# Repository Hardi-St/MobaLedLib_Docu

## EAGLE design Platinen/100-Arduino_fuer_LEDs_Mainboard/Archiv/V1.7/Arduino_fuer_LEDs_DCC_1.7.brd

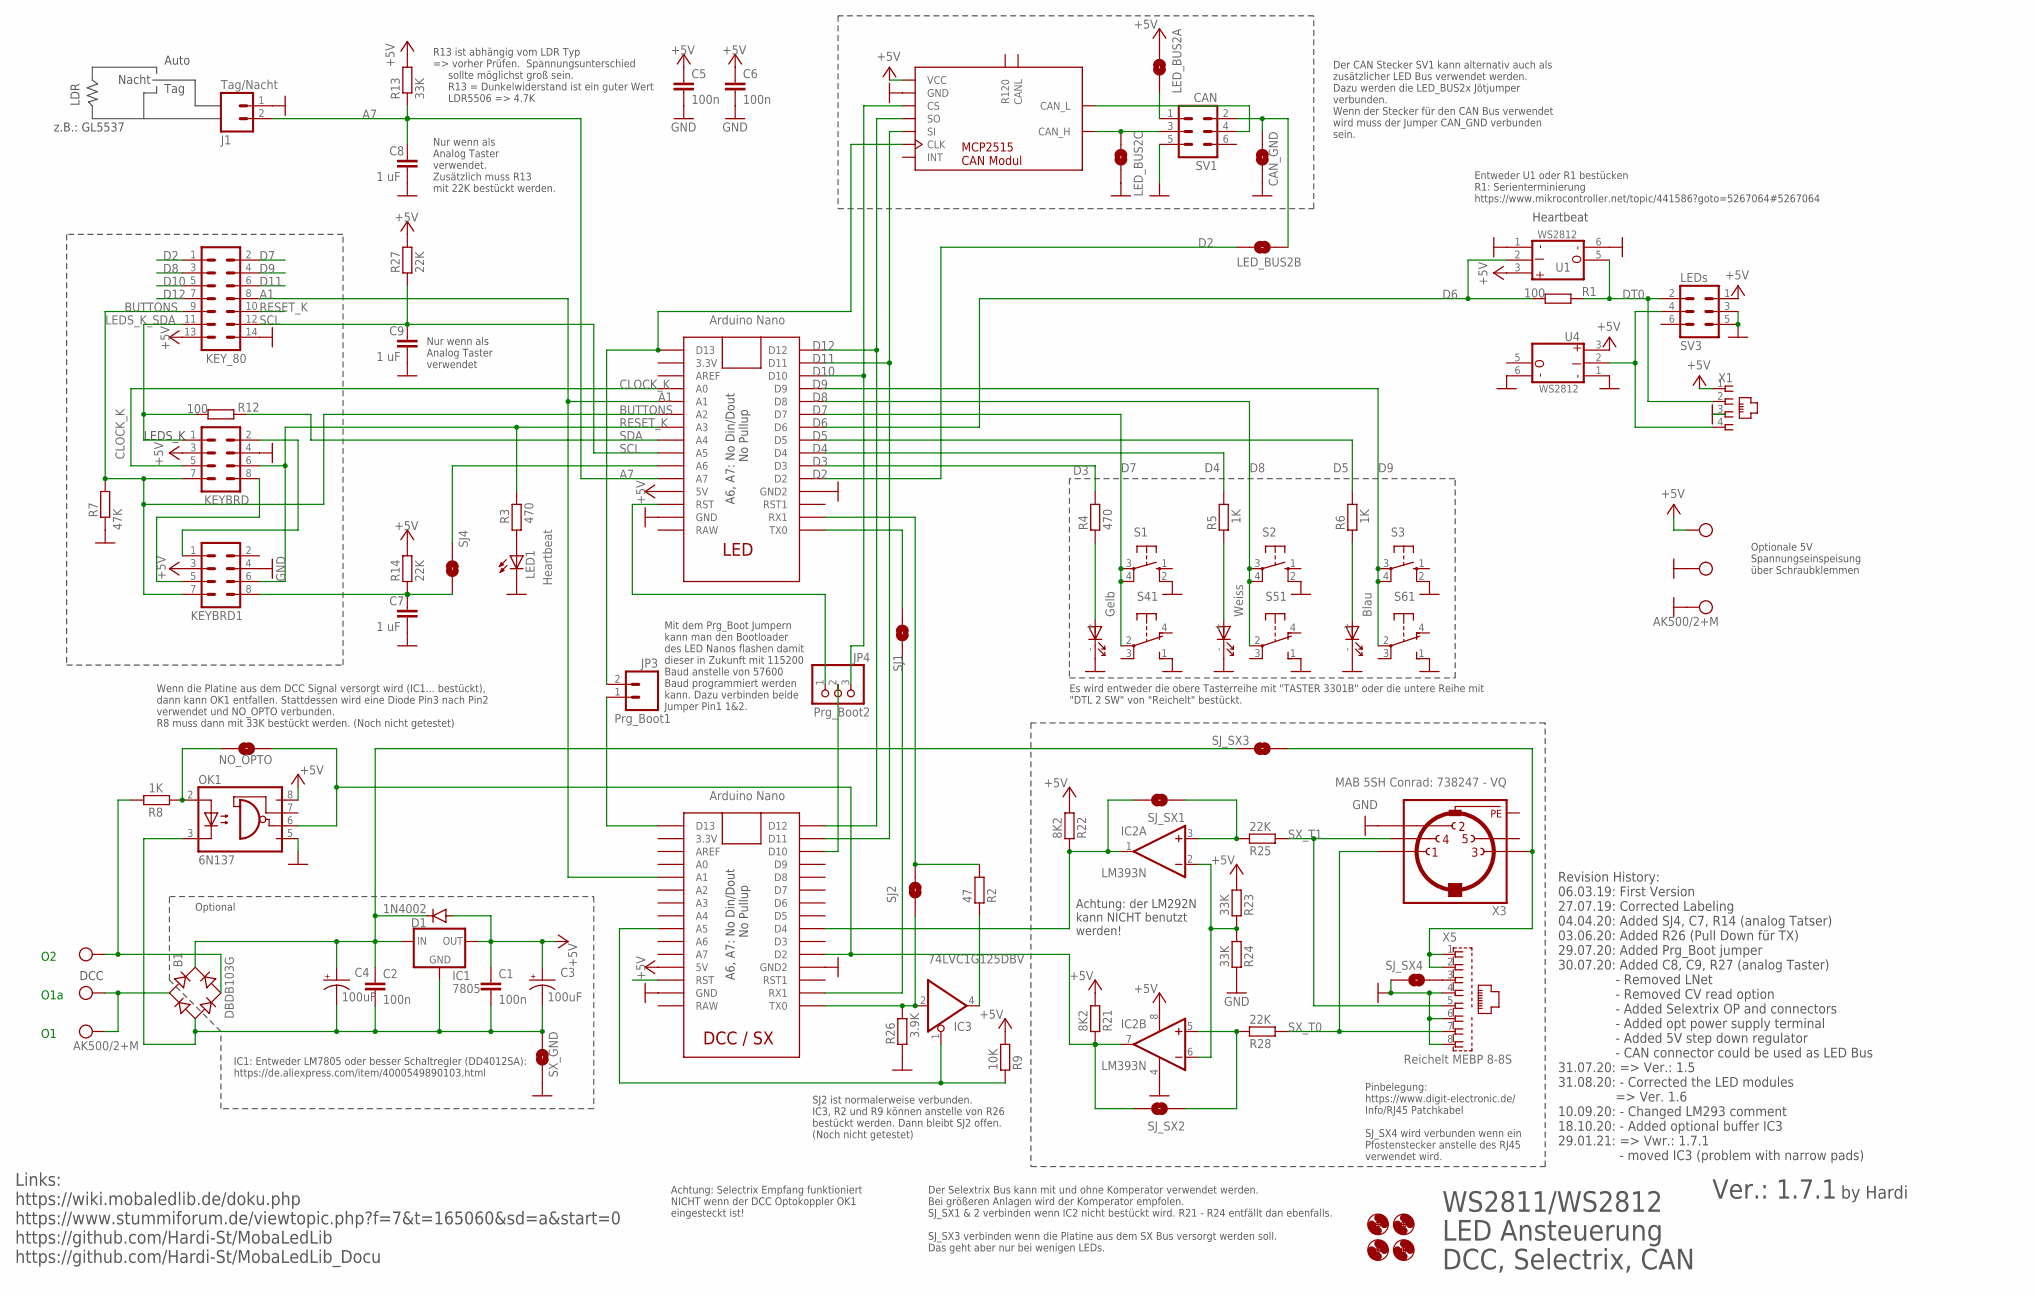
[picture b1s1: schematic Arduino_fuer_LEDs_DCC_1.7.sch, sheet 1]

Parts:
B1: DBDB103G; DB
C1, C2, C5, C6: 100n; C025-025X050
C3, C4: 100uF; SPARKFUN-CAPACITORS_CPOL-RADIAL-100UF-25V
C7, C8, C9: 1 uF; C025-025X050
CAN2: MCP2515_CAN_MODUL
CAN_GND: SOLDERJUMPERNO; SJ_2S-NO
D1: 1N4002; DO41-10
H1, H2, H3, H4: MOUNT-HOLE3.0; 3,0
IC1: 7805; 78XXS
IC2: LM393N; DIL08
IC3: 74LVC1G125DBV; SOT23-5
J1: Tag/Nacht; 1X02
JP3: Prg_Boot1; 1X02
JP4: Prg_Boot2; 1X03-CLEANBIG
KEYBRD, KEYBRD1: CON-HARTING-ML_ML08
KEY_80: ML14
LED1: Heartbeat; LED3MM
LED_BUS2A, LED_BUS2B, LED_BUS2C: SOLDERJUMPERNO; SJ_2S-NO
NO_OPTO: SOLDERJUMPERNO; SJ_2S-NO
OK1: 6N137; DIL08
R1, R12: 100; 0204/7
R2: 47; 0204/7
R3, R4: 470; 0204/7
R5, R6, R8: 1K; 0204/7
R7: 47K; 0204/7
R9: 10K; 0204/5
R13: 33K; 0204/7
R14, R27: 22K; 0204/7
R21, R22: 8K2; 0207/2V
R23, R24: 33K; 0207/2V
R25, R28: 22K; 0207/2V
R26: 3.9K; 0204/7
S1, S2, S3: 10-XX; B3F-10XX
S4: Gelb; SRKL
S5: Weiss; SRKL
S6: Blau; SRKL
SJ1, SJ2, SJ4: SOLDERJUMPERNO; SJ_2S-NO
SJ_SX1, SJ_SX2, SJ_SX3, SJ_SX4: SOLDERJUMPERNO; SJ_2S-NO
SV1: CAN; ML6
SV3: LEDs; ML6
SX_GND: SOLDERJUMPERNO; SJ_2S-NO
U1, U4: WS2812_MODUL; WS2812_LED_MODUL
U2: LED NANO; NANO
U3: DCC NANO; NANO
X1: RJ10
X2, X4: AK500/2+M
X3: MAB 5SH Conrad: 738247 - VQ; MAB5SH
X5: Reichelt MEBP 8-8S; RJ45_MEBP8-8S

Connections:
+5V: C1.1, C3.1 (+), C5.1, C6.1, CAN2.1 (VCC), D1.A, IC1.OUT, IC2.8 (V+), IC3.5 (VCC), KEYBRD.3, KEYBRD1.3, KEY_80.13, LED_BUS2A.1, OK1.8 (VCC), R9.2, R13.2, R14.2, R21.2, R22.2, R23.2, R27.2, SV3.1, U1.3 (VDD), U2.5V, U3.5V, U4.3 (VDD), X1.1, X4.2; also elsewhere on the board
A1: KEY_80.8, U2.A1, U3.A1
A7: C8.1, J1.2, R13.1, U2.A7
BUTTONS: KEYBRD.7, KEYBRD1.7, KEY_80.9, R7.2, U2.A2
CAN_H: CAN2.9 (CAN_H), LED_BUS2C.1, SV1.3
CAN_L: CAN2.8 (CAN_L), SV1.4
CLOCK_K: KEYBRD.5, U2.A0
D2: KEY_80.1, LED_BUS2B.1, U2.D2
D3: R4.2, U2.D3
D4: R5.2, U2.D4
D5: R6.2, U2.D5
D6: R1.2, U1.2 (DIN), U2.D6
D7: KEY_80.2, S1.3, S1.4 (P1), S4.2, U2.D7
D8: KEY_80.3, S2.3, S2.4 (P1), S5.2, U2.D8
D9: KEY_80.4, S3.3, S3.4 (P1), S6.2, U2.D9
D10: CAN2.3 (CS), JP4.3, KEY_80.5, U2.D10
D11: CAN2.5 (SI), KEY_80.6, U2.D11, U3.D11
D12: CAN2.4 (SO), KEY_80.7, U2.D12, U3.D12
DT0: R1.1, SV3.2, U1.5 (DO), X1.2; also elsewhere on the board
GND: C5.2, C6.2, C7.2, C8.2, C9.2, CAN2.2 (GND), CAN_GND.2, IC2.4 (V-), IC3.3 (GND), J1.1, KEYBRD.4, KEYBRD1.4, KEY_80.14, LED1.K (C), LED_BUS2C.2, OK1.5 (GND), R7.1, R24.1, R26.1, S1.2 (S1), S2.2 (S1), S3.2 (S1), S4.1 (S), S4.- (C), S5.1 (S), S5.- (C), S6.1 (S), S6.- (C), SJ_SX4.2, SV1.5, SV3.3, SV3.5, SX_GND.2, U1.1 (GND), U1.6 (GND1), U2.GND, U2.GND1 (GND2), U3.GND, U3.GND1 (GND2), U4.1 (GND), U4.6 (GND1), X1.3, X3.2, X4.1, X4.M, X5.4, X5.6, X5.8; also elsewhere on the board
LEDS_K_SDA: KEYBRD.1, KEY_80.11, R12.2
unnamed: SJ1.2, U2.TX0
unnamed: SJ_SX4.1, X5.3
unnamed: IC3.1 (OE), R9.1, U3.A5
unnamed: R4.1, S4.+ (A)
unnamed: CAN2.6 (CLK), JP3.2, U2.D13
unnamed: R5.1, S5.+ (A)
unnamed: R6.1, S6.+ (A)
unnamed: IC2.7 (OUT), NO_OPTO.1, OK1.6 (VO), R21.1, SJ_SX2.2, U3.D2
unnamed: LED_BUS2A.2, SV1.1
unnamed: SV3.4, U4.2 (DIN), X1.4
unnamed: B1.AC2, R8.2, X2.2
unnamed: B1.AC1, X2.1, X2.M
unnamed: B1.+, C2.1, C4.1 (+), D1.C, IC1.IN, SJ_SX3.2
unnamed: JP4.1, U2.RST
unnamed: IC2.1 (OUT), R22.1, SJ_SX1.2, U3.D4
unnamed: B1.-, C1.2, C2.2, C3.2 (-), C4.2 (-), IC1.GND, OK1.3 (C), SX_GND.1
unnamed: SJ1.1, U3.RX1
unnamed: LED1.A, R3.1
unnamed: JP3.1, U3.D13
unnamed: NO_OPTO.2, OK1.2 (A), R8.1
unnamed: C7.1, KEYBRD1.8, R14.1, SJ4.2
unnamed: KEYBRD.2, KEYBRD1.1
unnamed: KEYBRD.8, KEYBRD1.5
unnamed: SJ_SX3.1, X3.3, X5.1, X5.2
unnamed: SJ4.1, U2.A6
unnamed: JP4.2, U3.D10
unnamed: CAN_GND.1, LED_BUS2B.2, SV1.2
unnamed: IC3.2 (I), R26.2, SJ2.1, U3.TX0
unnamed: IC3.4 (O), R2.1
unnamed: R2.2, SJ2.2, U2.RX1
unnamed: IC2.2 (-IN), IC2.6 (-IN), R23.1, R24.2
unnamed: IC2.3 (+IN), R25.1, SJ_SX1.1
unnamed: IC2.5 (+IN), R28.1, SJ_SX2.1
PE: X3.PE, X3.PE@ (PE)
RESET_K: KEYBRD.6, KEYBRD1.6, KEY_80.10, R3.2, U2.A3
SCL: C9.1, KEY_80.12, R27.1, U2.A5
SDA: R12.1, U2.A4
SX_T0: R28.2, X3.1, X5.7
SX_T1: R25.2, X3.4, X5.5

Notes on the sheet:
WS2811/WS2812 LED Ansteuerung DCC, Selectrix, CAN
Es wird entweder die obere Tasterreihe mit "TASTER 3301B" oder die untere Reihe mit "DTL 2 SW" von "Reichelt" bestückt.
A6, A7: No Din/Dout No Pullup
Ver.: 1.7.1
LDR
Auto
Nacht
Tag
Entweder U1 oder R1 bestücken R1: Serienterminierung https://www.mikrocontroller.net/topic/441586?goto=5267064#5267064
Heartbeat
DCC
LEDS_K
Revision History: 06.03.19: First Version 27.07.19: Corrected Labeling 04.04.20: Added SJ4, C7, R14 (analog Tatser) 03.06.20: Added R26 (Pull Down für TX) 29.07.20: Added Prg_Boot jumper 30.07.20: Added C8, C9, R27 (analog Taster) - Removed LNet - Removed CV read option - Added Selextrix OP and con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
O1a
z.B.: GL5537
R13 ist abhängig vom LDR Typ => vorher Prüfen. Spannungsunterschied sollte möglichst groß sein. R13 = Dunkelwiderstand ist ein guter Wert LDR5506 => 4.7K
Nur wenn als Analog Taster verwendet. Zusätzlich muss R13 mit 22K bestückt werden.
Optional
Nur wenn als Analog Taster verwendet
Der CAN Stecker SV1 kann alternativ auch als zusätzlicher LED Bus verwendet werden. Dazu werden die LED_BUS2x Jötjumper verbunden. Wenn der Stecker für den CAN Bus verwendet wird muss der Jumper CAN_GND verbunden sein.
Pinbelegung: https://www.digit-electronic.de/ Info/RJ45 Patchkabel SJ_SX4 wird verbunden wenn ein Pfostenstecker anstelle des RJ45 verwendet wird.
IC1: Entweder LM7805 oder besser Schaltregler (DD4012SA): https://de.aliexpress.com/item/4000549890103.html
Optionale 5V Spannungseinspeisung über Schraubklemmen
by Hardi
Links: https://wiki.mobaledlib.de/doku.php https://www.stummiforum.de/viewtopic.php?f=7&t=165060&sd=a&start=0 https://github.com/Hardi-St/MobaLedLib https://github.com/Hardi-St/MobaLedLib_Docu
Mit dem Prg_Boot Jumpern kann man den Bootloader des LED Nanos flashen damit dieser in Zukunft mit 115200 Baud anstelle von 57600 Baud programmiert werden kann. Dazu verbinden beide Jumper Pin1 1&2.
LED
DCC / SX
Der Selextrix Bus kann mit und ohne Komperator verwendet werden. Bei größeren Anlagen wird der Komperator empfolen. SJ_SX1 & 2 verbinden wenn IC2 nicht bestückt wird. R21 - R24 entfällt dan ebenfalls. SJ_SX3 verbinden wenn die Platine aus dem SX Bus versorgt werden soll. Das geht aber nur bei wenig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
Wenn die Platine aus dem DCC Signal versorgt wird (IC1... bestückt), dann kann OK1 entfallen. Stattdessen wird eine Diode Pin3 nach Pin2 verwendet und NO_OPTO verbunden. R8 muss dann mit 33K bestückt werden. (Noch nicht getestet)
Achtung: der LM292N kann NICHT benutzt werden!
SJ2 ist normalerweise verbunden. IC3, R2 und R9 können anstelle von R26 bestückt werden. Dann bleibt SJ2 offen. (Noch nicht getestet)
Achtung: Selectrix Empfang funktioniert NICHT wenn der DCC Optokoppler OK1 eingesteckt ist!

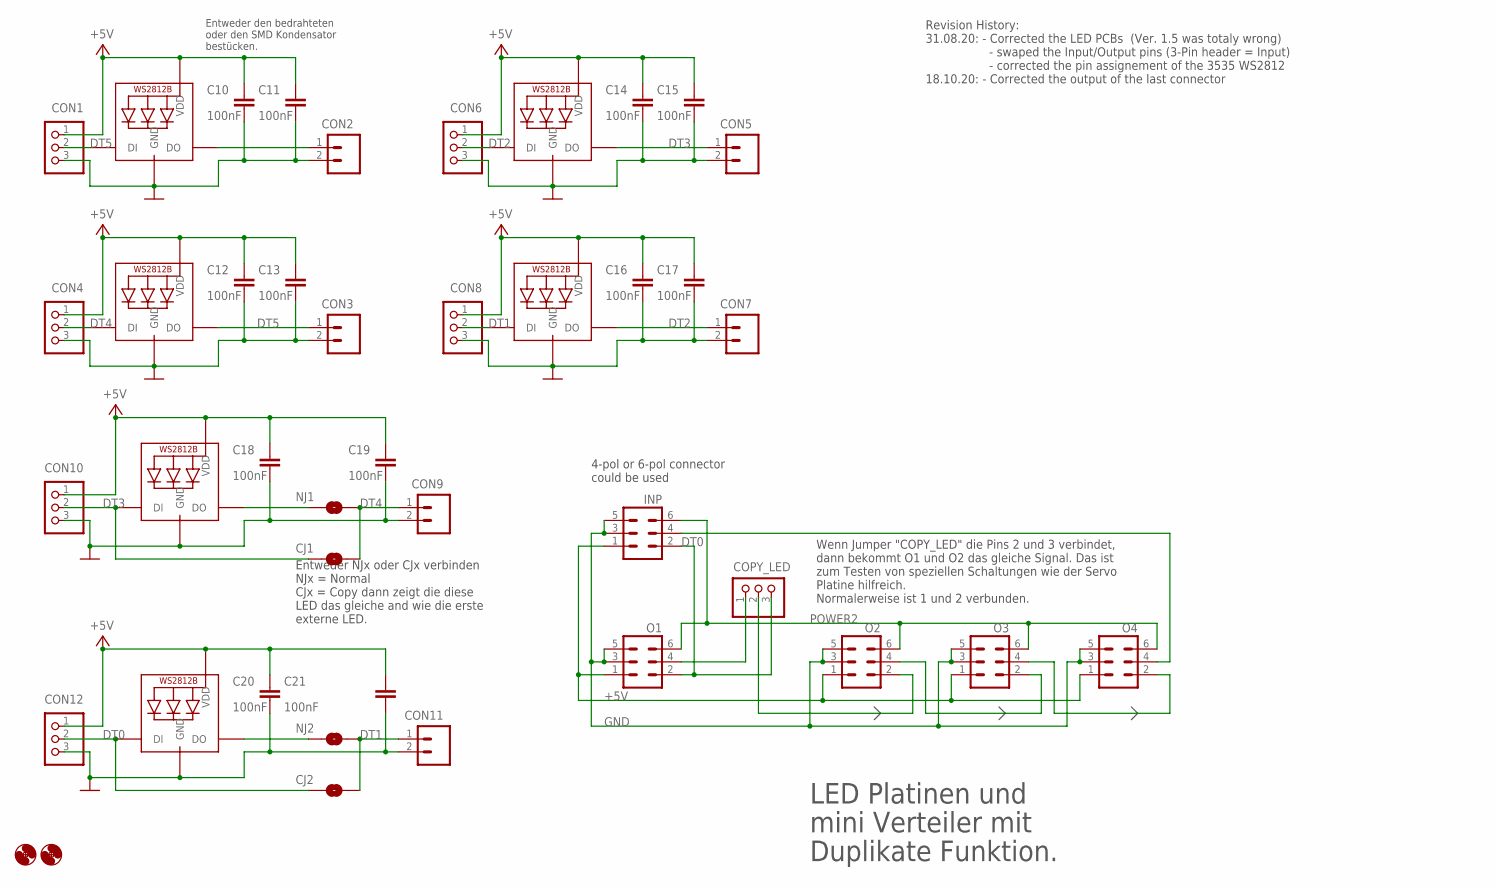
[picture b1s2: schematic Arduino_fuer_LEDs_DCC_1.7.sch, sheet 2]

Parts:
C10, C12, C14, C16, C18, C20: 100nF; C025-025X050
C11, C13, C15, C17, C19, C21: 100nF; C1206
CJ1, CJ2: SOLDERJUMPERNO; SJ_2S-NO
CON1, CON4, CON6, CON8, CON10, CON12: PINHD-1X3CB; 1X03-CLEANBIG
CON2, CON3, CON5, CON7, CON9, CON11: M02PTH; 1X02
COPY_LED: PINHD-1X3CB; 1X03-CLEANBIG
H5, H6: MOUNT-HOLE3.0; 3,0
INP: ML6
LED2, LED3, LED6: WS2812B5050; WS2812B
LED4, LED5, LED7: WS2812B3535; LED3535
NJ1, NJ2: SOLDERJUMPERNO; SJ_2S-NO
O1, O2, O3, O4: ML6

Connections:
+5V: C10.1, C11.1, C12.1, C13.1, C14.1, C15.1, C16.1, C17.1, C18.1, C19.1, C20.1, C21.1, CON1.1, CON4.1, CON6.1, CON8.1, CON10.1, CON12.1, INP.1, LED2.1-5V (VDD), LED3.1-5V (VDD), LED4.1_5V (VDD), LED5.1_5V (VDD), LED6.1-5V (VDD), LED7.1_5V (VDD), O1.1, O2.1, O3.1, O4.1; also elsewhere on the board
DT0: CJ2.1, CON12.2, COPY_LED.3, INP.2, LED7.4_DIN (DI), O1.2; also elsewhere on the board
DT1: CJ2.2, CON8.2, CON11.1, LED5.4_DIN (DI), NJ2.2
DT2: CON6.2, CON7.1, LED4.4_DIN (DI), LED5.2_DOUT (DO)
DT3: CJ1.1, CON5.1, CON10.2, LED4.2_DOUT (DO), LED6.4-DIN (DI)
DT4: CJ1.2, CON4.2, CON9.1, LED3.4-DIN (DI), NJ1.2
DT5: CON1.2, CON3.1, LED2.4-DIN (DI), LED3.2-DOUT (DO)
GND: C10.2, C11.2, C12.2, C13.2, C14.2, C15.2, C16.2, C17.2, C18.2, C19.2, C20.2, C21.2, CON1.3, CON2.2, CON3.2, CON4.3, CON5.2, CON6.3, CON7.2, CON8.3, CON9.2, CON10.3, CON11.2, CON12.3, INP.3, INP.5, LED2.3-GND (GND), LED3.3-GND (GND), LED4.3_GND (GND), LED5.3_GND (GND), LED6.3-GND (GND), LED7.3_GND (GND), O1.3, O1.5, O2.3, O2.5, O3.3, O3.5, O4.3, O4.5; also elsewhere on the board
unnamed: O3.4, O4.2
unnamed: CON2.1, LED2.2-DOUT (DO)
unnamed: LED6.2-DOUT (DO), NJ1.1
unnamed: INP.4, O4.4
unnamed: COPY_LED.2, O2.2
unnamed: LED7.2_DOUT (DO), NJ2.1
unnamed: O2.4, O3.2
unnamed: COPY_LED.1, O1.4
POWER2: INP.6, O1.6, O2.6, O3.6, O4.6

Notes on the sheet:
Entweder den bedrahteten oder den SMD Kondensator bestücken.
4-pol or 6-pol connector could be used
LED Platinen und mini Verteiler mit Duplikate Funktion.
Wenn Jumper "COPY_LED" die Pins 2 und 3 verbindet, dann bekommt O1 und O2 das gleiche Signal. Das ist zum Testen von speziellen Schaltungen wie der Servo Platine hilfreich. Normalerweise ist 1 und 2 verbunden.
Entweder NJx oder CJx verbinden NJx = Normal CJx = Copy dann zeigt die diese LED das gleiche and wie die erste externe LED.
Revision History: 31.08.20: - Corrected the LED PCBs (Ver. 1.5 was totaly wrong) - swaped the Input/Output pins (3-Pin header = Input) - corrected the pin assignement of the 3535 WS2812 18.10.20: - Corrected the output of the last connector

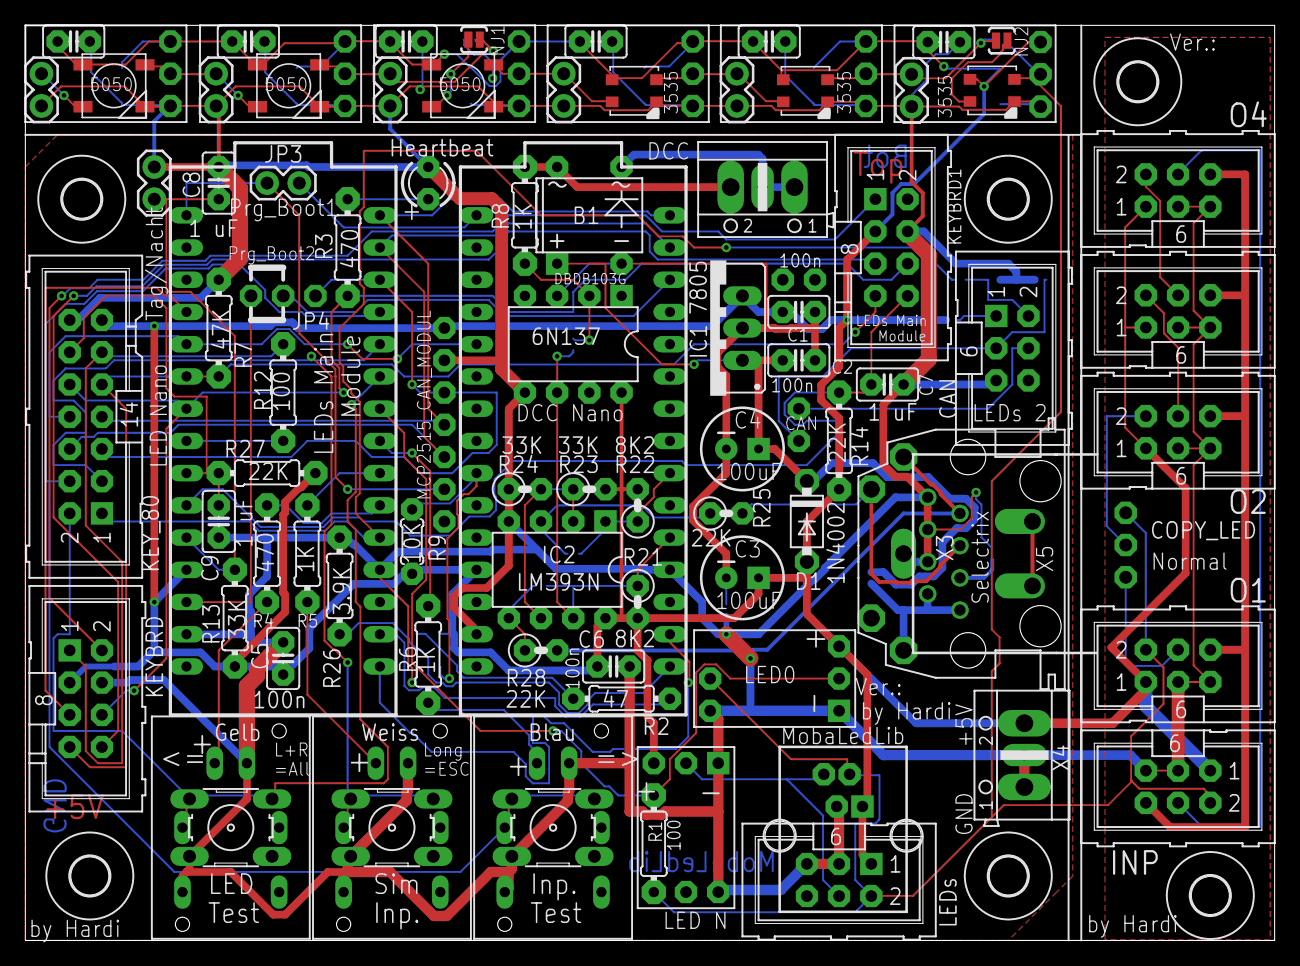
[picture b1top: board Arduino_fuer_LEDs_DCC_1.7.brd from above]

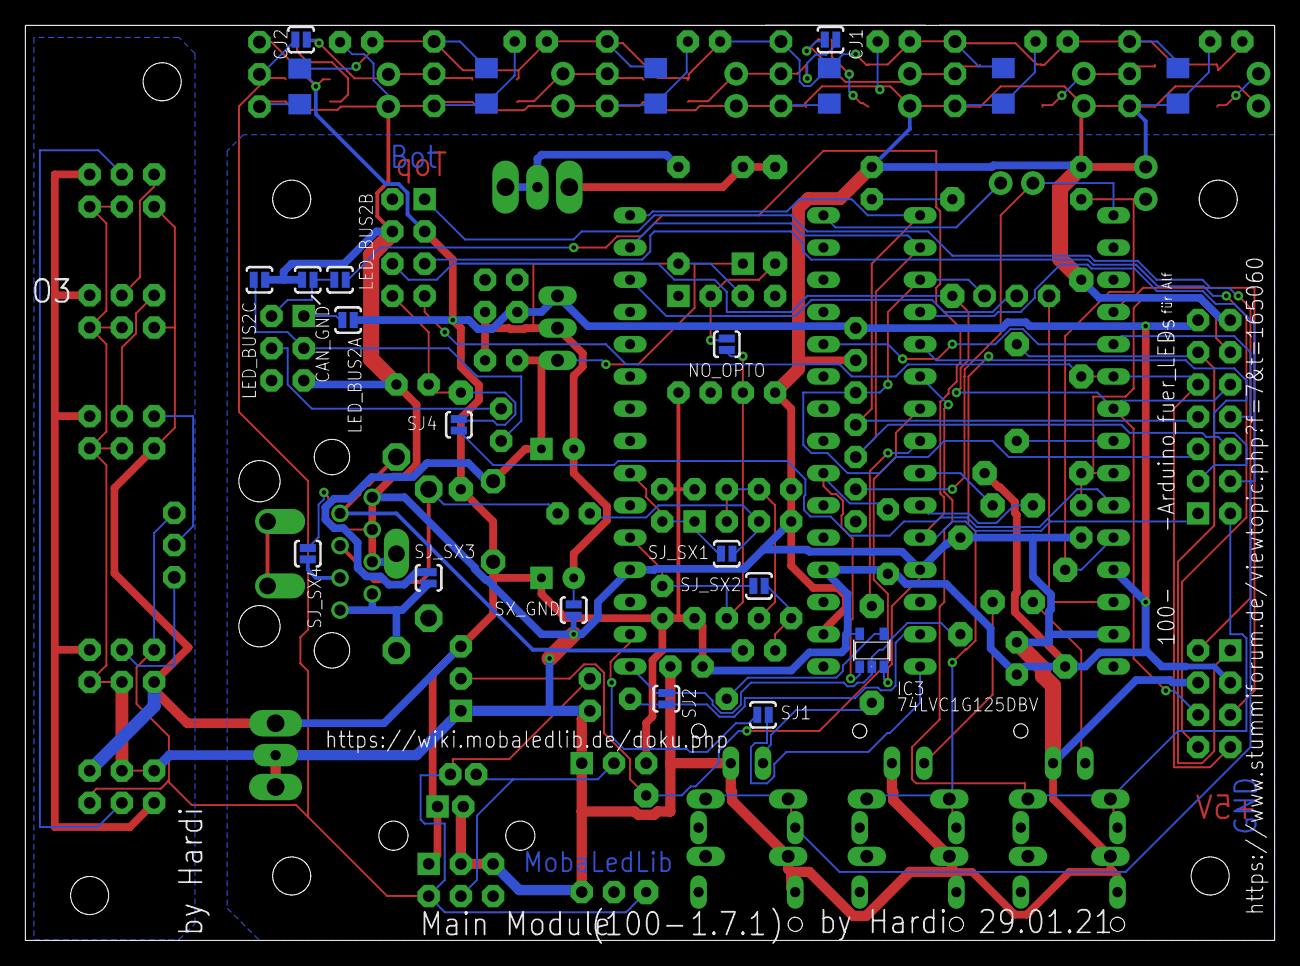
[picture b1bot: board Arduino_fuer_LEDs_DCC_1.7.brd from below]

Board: 2 copper layers, 98.5 x 72.1 mm, 119 parts (22 on the bottom side), 74 nets.

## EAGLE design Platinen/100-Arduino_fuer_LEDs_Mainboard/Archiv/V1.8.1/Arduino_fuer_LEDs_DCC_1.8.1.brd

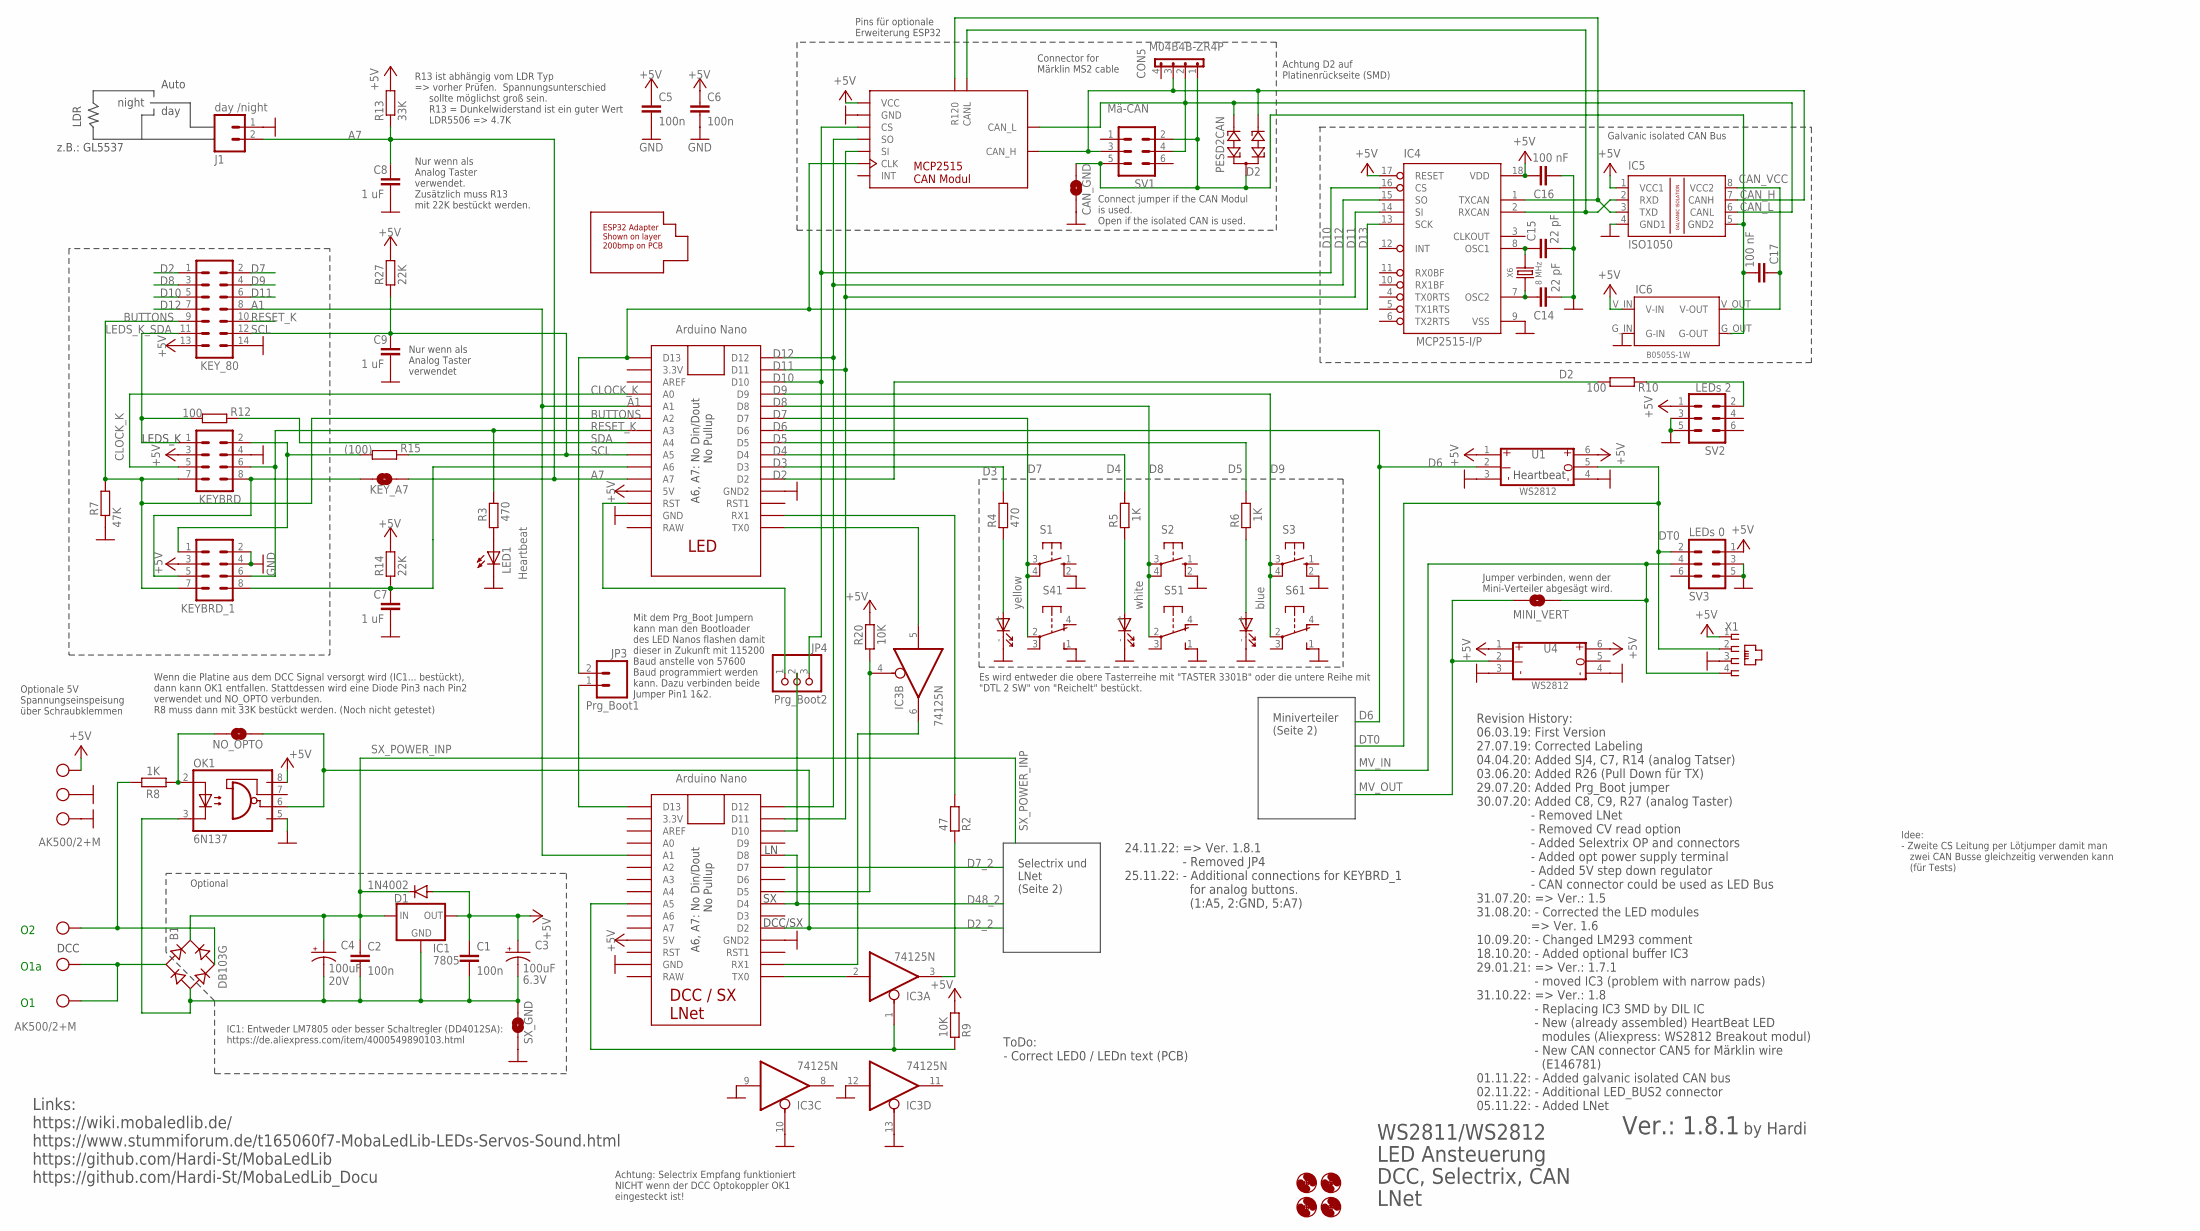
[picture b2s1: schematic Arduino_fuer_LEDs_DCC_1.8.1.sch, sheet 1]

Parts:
B1: DB103G; DB
C1, C2, C5, C6: 100n; C025-025X050
C3: 100uF; SPARKFUN-CAPACITORS_CPOL-RADIAL-100UF-25V; VOLTAGE 6.3V
C4: 100uF; SPARKFUN-CAPACITORS_CPOL-RADIAL-100UF-25V; VOLTAGE 20V
C7, C8, C9: 1 uF; C025-025X050
C14, C15: 22 pF; C2.5-2
C16, C17: 100 nF; C2.5-2
CAN2: MCP2515_CAN_MODUL
CAN_GND: SOLDERJUMPERNO; SJ_2S-NO
CON5: M04B4B-ZR4P; B4B-ZR4P
D1: 1N4002; DO41-10
D2: PESD2CAN; SOT23
H1, H2, H3, H4: MOUNT-HOLE3.0; 3,0
IC1: 7805; 78XXS
IC3: 74125N; DIL14
IC4: MCP2515-I/P; DIL18
IC5: ISO1050; DIL08
IC6: B0505S-1W; DCDC-TEA_NME
J1: day /night; 1X02
JP3: Prg_Boot1; 1X02
JP4: Prg_Boot2; 1X03-CLEANBIG
KEYBRD: CON-HARTING-ML_ML08
KEYBRD_1: CON-HARTING-ML_ML08
KEY_80: ML14
KEY_A7: SOLDERJUMPERNO; SJ_2S-NO
LED1: Heartbeat; LED3MM
MINI_VERT: SOLDERJUMPERNO; SJ_2S-NO
NO_OPTO: SOLDERJUMPERNO; SJ_2S-NO
OK1: 6N137; DIL08
R2: 47; 0204/7
R3, R4: 470; 0204/7
R5, R6, R8: 1K; 0204/7
R7: 47K; 0204/7
R9: 10K; 0204/7
R10, R12: 100; 0204/7
R13: 33K; 0204/7
R14, R27: 22K; 0204/7
R15: (100); 0204/7
R20: 10K; 0207/2V
S1, S2, S3: 10-XX; B3F-10XX
S4: yellow; SRKL
S5: white; SRKL
S6: blue; SRKL
SV1: Mä-CAN; ML6
SV2: LEDs 2; ML6
SV3: LEDs 0; ML6
SX_GND: SOLDERJUMPERNO; SJ_2S-NO
U1, U4: WS2812_BREAKOUT; WS2812__BREAKOUT
U2: LED NANO; NANO
U3: DCC NANO; NANO
U$1: ESP_ADAPTER
X1: RJ10
X2, X4: AK500/2+M
X6: 8 MHz; HC49U-V

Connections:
+5V: C1.1, C3.1 (+), C5.1, C6.1, C16.1, CAN2.1 (VCC), D1.A, IC1.OUT, IC3.14 (VCC), IC4.17 (RESET), IC4.18 (VDD), IC5.1 (VCC1), IC6.V_IN (V-IN), KEYBRD.3, KEYBRD_1.3, KEY_80.13, OK1.8 (VCC), R9.2, R13.2, R14.2, R20.1, R27.2, SV2.1, SV3.1, U1.1 (VDD1), U1.6 (VDD), U2.5V, U3.5V, U4.1 (VDD1), U4.6 (VDD), X1.1, X4.2; also elsewhere on the board
A1: KEY_80.8, U2.A1, U3.A1
A7: C8.1, J1.2, KEY_A7.1, R13.1, U2.A7
BUTTONS: KEYBRD.7, KEYBRD_1.7, KEY_80.9, R7.2, U2.A2
CAN_H: CAN2.9 (CAN_H), CON5.3, D2.1, IC5.7 (CANH), SV1.3
CAN_L: CAN2.8 (CAN_L), CON5.2, D2.2, IC5.6 (CANL), SV1.4
CAN_VCC: C17.1, IC5.8 (VCC2), IC6.V_OUT (V-OUT)
CLOCK_K: KEYBRD.5, U2.A0
D2: KEY_80.1, R10.2, U2.D2
D2_2: NO_OPTO.1, OK1.6 (VO), U3.D2; also elsewhere on the board
D3: R4.2, U2.D3
D4: R5.2, U2.D4
D5: R6.2, U2.D5
D6: U1.2 (DIN), U2.D6
D7: KEY_80.2, S1.3, S1.4 (P1), S4.2, U2.D7
D7_2: U3.D7; also elsewhere on the board
D8: KEY_80.3, S2.3, S2.4 (P1), S5.2, U2.D8
D9: KEY_80.4, S3.3, S3.4 (P1), S6.2, U2.D9
D10: CAN2.3 (CS), IC4.16 (CS), JP4.3, KEY_80.5, U2.D10
D11: CAN2.5 (SI), IC4.14 (SI), KEY_80.6, U2.D11, U3.D11
D12: CAN2.4 (SO), IC4.15 (SO), KEY_80.7, U2.D12, U3.D12
D13: CAN2.6 (CLK), IC4.13 (SCK), JP3.2, U2.D13
D48_2: U3.D4, U3.D8; also elsewhere on the board
DCC/SX_GND: B1.-, C1.2, C2.2, C3.2 (-), C4.2 (-), IC1.GND, OK1.3 (C), SX_GND.1
DT0: SV3.2, U1.5 (DO), X1.2
GND: C5.2, C6.2, C7.2, C8.2, C9.2, C14.2, C15.2, C16.2, CAN2.2 (GND), CAN_GND.2, IC3.7 (GND), IC3.9 (I), IC3.10 (OE), IC3.12 (I), IC3.13 (OE), IC4.9 (VSS), IC5.4 (GND1), IC6.G_IN (G-IN), J1.1, KEYBRD.4, KEYBRD_1.2, KEYBRD_1.4, KEY_80.14, LED1.K (C), OK1.5 (GND), R7.1, S1.2 (S1), S2.2 (S1), S3.2 (S1), S4.1 (S), S4.- (C), S5.1 (S), S5.- (C), S6.1 (S), S6.- (C), SV2.3, SV2.5, SV3.3, SV3.5, SX_GND.2, U1.3 (GND1), U1.4 (GND), U2.GND, U2.GND1 (GND2), U3.GND, U3.GND1 (GND2), U4.3 (GND1), U4.4 (GND), X1.3, X4.1, X4.M; also elsewhere on the board
GND2: C17.2, CAN_GND.1, CON5.1, D2.3, IC5.5 (GND2), IC6.G_OUT (G-OUT), SV1.2, SV1.5
LEDS_K_SDA: KEYBRD.1, KEY_80.11, R12.2
MV_IN: MINI_VERT.2, SV3.4, X1.4; also elsewhere on the board
MV_OUT: MINI_VERT.1, U4.2 (DIN); also elsewhere on the board
unnamed: IC3.5 (I), U2.TX0
unnamed: IC3.1 (OE), R9.1, U3.A5
unnamed: R4.1, S4.+ (A)
unnamed: R10.1, SV2.2
unnamed: R5.1, S5.+ (A)
unnamed: R6.1, S6.+ (A)
unnamed: B1.AC1, X2.1, X2.M
unnamed: B1.AC2, R8.2, X2.2
unnamed: JP4.1, U2.RST
unnamed: IC3.4 (OE), R20.2, U3.D5
unnamed: IC3.6 (O), U3.RX1
unnamed: LED1.A, R3.1
unnamed: JP3.1, U3.D13
unnamed: NO_OPTO.2, OK1.2 (A), R8.1
unnamed: KEYBRD.2, KEYBRD_1.1, R15.2
unnamed: KEYBRD.8, KEYBRD_1.5, KEY_A7.2
unnamed: C7.1, KEYBRD_1.8, R14.1, U2.A6
unnamed: JP4.2, U3.D10
unnamed: IC3.2 (I), U3.TX0
unnamed: IC3.3 (O), R2.1
unnamed: R2.2, U2.RX1
OSC1: C15.1, IC4.8 (OSC1), X6.2
OSC2: C14.1, IC4.7 (OSC2), X6.1
RESET_K: KEYBRD.6, KEYBRD_1.6, KEY_80.10, R3.2, U2.A3
RXCAN: CAN2.11 (CANL), IC4.2 (RXCAN), IC5.2 (RXD)
SCL: C9.1, KEY_80.12, R15.1, R27.1, U2.A5
SDA: R12.1, U2.A4
SX_POWER_INP: B1.+, C2.1, C4.1 (+), D1.C, IC1.IN; also elsewhere on the board
TXCAN: CAN2.10 (R120), IC4.1 (TXCAN), IC5.3 (TXD)

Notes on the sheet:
WS2811/WS2812 LED Ansteuerung DCC, Selectrix, CAN LNet
Es wird entweder die obere Tasterreihe mit "TASTER 3301B" oder die untere Reihe mit "DTL 2 SW" von "Reichelt" bestückt.
A6, A7: No Din/Dout No Pullup
Ver.: 1.8.1
LDR
Auto
night
day
Heartbeat
DCC
LEDS_K
Revision History: 06.03.19: First Version 27.07.19: Corrected Labeling 04.04.20: Added SJ4, C7, R14 (analog Tatser) 03.06.20: Added R26 (Pull Down für TX) 29.07.20: Added Prg_Boot jumper 30.07.20: Added C8, C9, R27 (analog Taster) - Removed LNet - Removed CV read option - Added Selextrix OP and con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
O1a
z.B.: GL5537
R13 ist abhängig vom LDR Typ => vorher Prüfen. Spannungsunterschied sollte möglichst groß sein. R13 = Dunkelwiderstand ist ein guter Wert LDR5506 => 4.7K
Nur wenn als Analog Taster verwendet. Zusätzlich muss R13 mit 22K bestückt werden.
Optional
Nur wenn als Analog Taster verwendet
IC1: Entweder LM7805 oder besser Schaltregler (DD4012SA): https://de.aliexpress.com/item/4000549890103.html
Optionale 5V Spannungseinspeisung über Schraubklemmen
by Hardi
Links: https://wiki.mobaledlib.de/ https://www.stummiforum.de/t165060f7-MobaLedLib-LEDs-Servos-Sound.html https://github.com/Hardi-St/MobaLedLib https://github.com/Hardi-St/MobaLedLib_Docu
Mit dem Prg_Boot Jumpern kann man den Bootloader des LED Nanos flashen damit dieser in Zukunft mit 115200 Baud anstelle von 57600 Baud programmiert werden kann. Dazu verbinden beide Jumper Pin1 1&2.
LED
DCC / SX LNet
Wenn die Platine aus dem DCC Signal versorgt wird (IC1... bestückt), dann kann OK1 entfallen. Stattdessen wird eine Diode Pin3 nach Pin2 verwendet und NO_OPTO verbunden. R8 muss dann mit 33K bestückt werden. (Noch nicht getestet)
Achtung: Selectrix Empfang funktioniert NICHT wenn der DCC Optokoppler OK1 eingesteckt ist!
Connector for Märklin MS2 cable
Connect jumper if the CAN Modul is used. Open if the isolated CAN is used.
Galvanic isolated CAN Bus
Jumper verbinden, wenn der Mini-Verteiler abgesägt wird.
Selectrix und LNet (Seite 2)
DCC/SX
Miniverteiler (Seite 2)
Achtung D2 auf Platinenrückseite (SMD)
24.11.22: => Ver. 1.8.1 - Removed JP4 25.11.22: - Additional connections for KEYBRD_1 for analog buttons. (1:A5, 2:GND, 5:A7)
Idee: - Zweite CS Leitung per Lötjumper damit man zwei CAN Busse gleichzeitig verwenden kann (für Tests)
Pins für optionale Erweiterung ESP32
ToDo: - Correct LED0 / LEDn text (PCB)

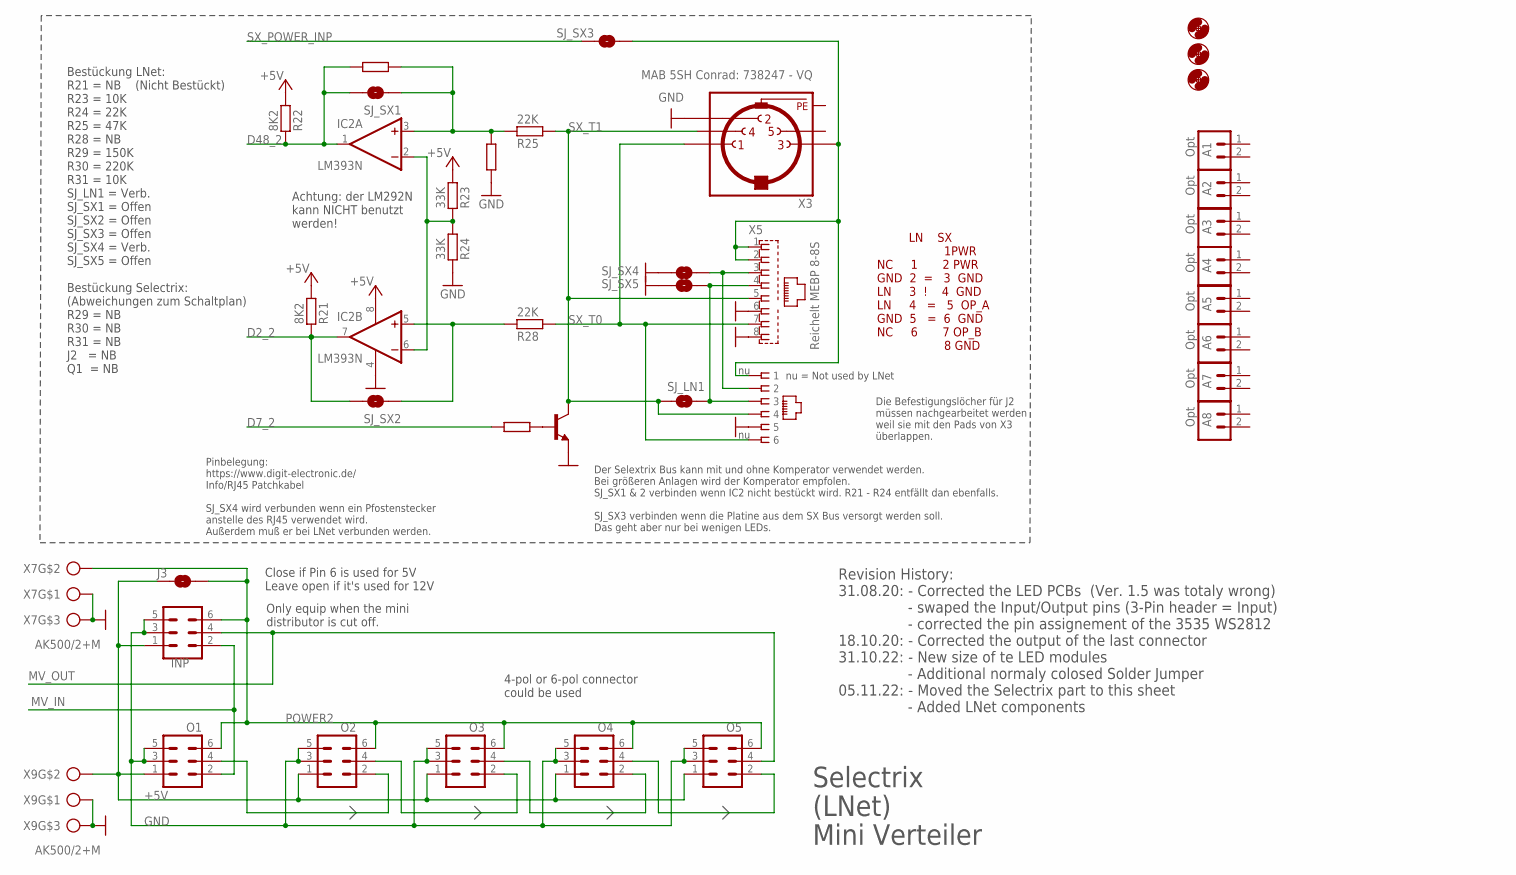
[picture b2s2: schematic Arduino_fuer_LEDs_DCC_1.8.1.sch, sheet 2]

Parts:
A1, A2, A3, A4, A5, A6, A7, A8: Opt; 1X02
H5, H6, H7: MOUNT-HOLE3.0; 3,0
IC2: LM393N; DIL08
INP: ML6
J2: LNet; RJ11-NO_SHIELD_NO_MOUNT_HOULE
J3: SOLDERJUMPERNO; SJ_2S-NO
O1, O2, O3, O4, O5: ML6
Q1: BC547; TO92
R21, R22: 8K2; 0207/2V
R23, R24: 33K; 0207/2V
R25, R28: 22K; 0207/2V
R29: 150K; 0207/2V
R30: 220K; 0207/2V
R31: 10K; 0207/2V
SJ_LN1: SOLDERJUMPERNO; SJ_2S-NO
SJ_SX1, SJ_SX2, SJ_SX3, SJ_SX4, SJ_SX5: SOLDERJUMPERNO; SJ_2S-NO
X3: MAB 5SH Conrad: 738247 - VQ; MAB5SH
X5: Reichelt MEBP 8-8S; RJ45_MEBP8-8S
X7, X9: AK500/2+M

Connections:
+5V: IC2.8 (V+), INP.1, J3.1, O1.1, O2.1, O3.1, O4.1, O5.1, R21.2, R22.2, R23.2, X9.2; also elsewhere on the board
D2_2: IC2.7 (OUT), R21.1, SJ_SX2.2; also elsewhere on the board
D7_2: R31.2; also elsewhere on the board
D48_2: IC2.1 (OUT), R22.1, R30.2, SJ_SX1.2; also elsewhere on the board
GND: IC2.4 (V-), INP.3, INP.5, J2.5, O1.3, O1.5, O2.3, O2.5, O3.3, O3.5, O4.3, O4.5, O5.3, O5.5, Q1.1 (E), R24.1, R29.1, SJ_SX4.2, SJ_SX5.2, X3.2, X5.6, X5.8, X7.1, X7.M, X9.1, X9.M; also elsewhere on the board
MV_IN: INP.2, O1.2; also elsewhere on the board
MV_OUT: INP.4, O5.4; also elsewhere on the board
unnamed: J2.1, SJ_SX3.1, X3.3, X5.1, X5.2
unnamed: J2.2, SJ_SX4.1, X5.3
unnamed: Q1.2 (B), R31.1
unnamed: O3.4, O4.2
unnamed: O1.4, O2.2
unnamed: O4.4, O5.2
unnamed: IC2.2 (-IN), IC2.6 (-IN), R23.1, R24.2
unnamed: IC2.3 (+IN), R25.1, R29.2, R30.1, SJ_SX1.1
unnamed: J2.3, SJ_LN1.1, SJ_SX5.1, X5.4
unnamed: IC2.5 (+IN), R28.1, SJ_SX2.1
unnamed: O2.4, O3.2
PE: X3.PE, X3.PE@ (PE)
POWER2: INP.6, J3.2, O1.6, O2.6, O3.6, O4.6, O5.6, X7.2
SX_POWER_INP: SJ_SX3.2; also elsewhere on the board
SX_T0: J2.6, R28.2, X3.1, X5.7
SX_T1: J2.4, Q1.3 (C), R25.2, SJ_LN1.2, X3.4, X5.5

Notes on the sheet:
4-pol or 6-pol connector could be used
Selectrix (LNet) Mini Verteiler
Revision History: 31.08.20: - Corrected the LED PCBs (Ver. 1.5 was totaly wrong) - swaped the Input/Output pins (3-Pin header = Input) - corrected the pin assignement of the 3535 WS2812 18.10.20: - Corrected the output of the last connector 31.10.22: - New size of te LED modules - Additional normal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
Pinbelegung: https://www.digit-electronic.de/ Info/RJ45 Patchkabel SJ_SX4 wird verbunden wenn ein Pfostenstecker anstelle des RJ45 verwendet wird. Außerdem muß er bei LNet verbunden werden.
Achtung: der LM292N kann NICHT benutzt werden!
Bestückung LNet: R21 = NB (Nicht Bestückt) R23 = 10K R24 = 22K R25 = 47K R28 = NB R29 = 150K R30 = 220K R31 = 10K SJ_LN1 = Verb. SJ_SX1 = Offen SJ_SX2 = Offen SJ_SX3 = Offen SJ_SX4 = Verb. SJ_SX5 = Offen Bestückung Selectrix: (Abweichungen zum Schaltplan) R29 = NB R30 = NB R31 = NB J2 = NB Q1 = NB
LN SX 1PWR NC 1 2 PWR GND 2 = 3 GND LN 3 ! 4 GND LN 4 = 5 OP_A GND 5 = 6 GND NC 6 7 OP_B 8 GND
Die Befestigungslöcher für J2 müssen nachgearbeitet werden weil sie mit den Pads von X3 überlappen.
Der Selextrix Bus kann mit und ohne Komperator verwendet werden. Bei größeren Anlagen wird der Komperator empfolen. SJ_SX1 & 2 verbinden wenn IC2 nicht bestückt wird. R21 - R24 entfällt dan ebenfalls. SJ_SX3 verbinden wenn die Platine aus dem SX Bus versorgt werden soll. Das geht aber nur bei wenig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
nu = Not used by LNet
Close if Pin 6 is used for 5V Leave open if it's used for 12V
Only equip when the mini distributor is cut off.

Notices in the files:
parts and their libraries:
SparkFun-Retired: Licensing:Creative Commons ShareAlike 4.0 International - https://creativecommons.org/licenses/by-sa/4.0
